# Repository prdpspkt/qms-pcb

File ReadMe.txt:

##This project is done to minimize cost of government office. In market normally Queue Management System costs 65k for manual type and more than 100k for dynamic. Also display, callpad cost extra 20k for each terminal.
This project uses a:
15k Token Printer
10k Android Device as Server
2k Terminal Display
1k Call Pad
-----------------
Total 28k

Paste content from footprints and symbols folder to respective folder in KiCad in documents directory.

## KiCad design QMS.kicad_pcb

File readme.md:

## Queue Management System
This project is done to minimize cost of government office. In market normally Queue Management System costs 65k for manual type and more than 100k for dynamic. Also display, call pad cost extra 20k for each terminal.

### Costing
- 15k Token Printer
- 10k Android Device as Server
- 2k Terminal Display
- 1k Call Pad
...........
- Total 28k

### Installation
Paste content from footprints and symbols folder to respective folder in KiCad in documents directory.

### Programming

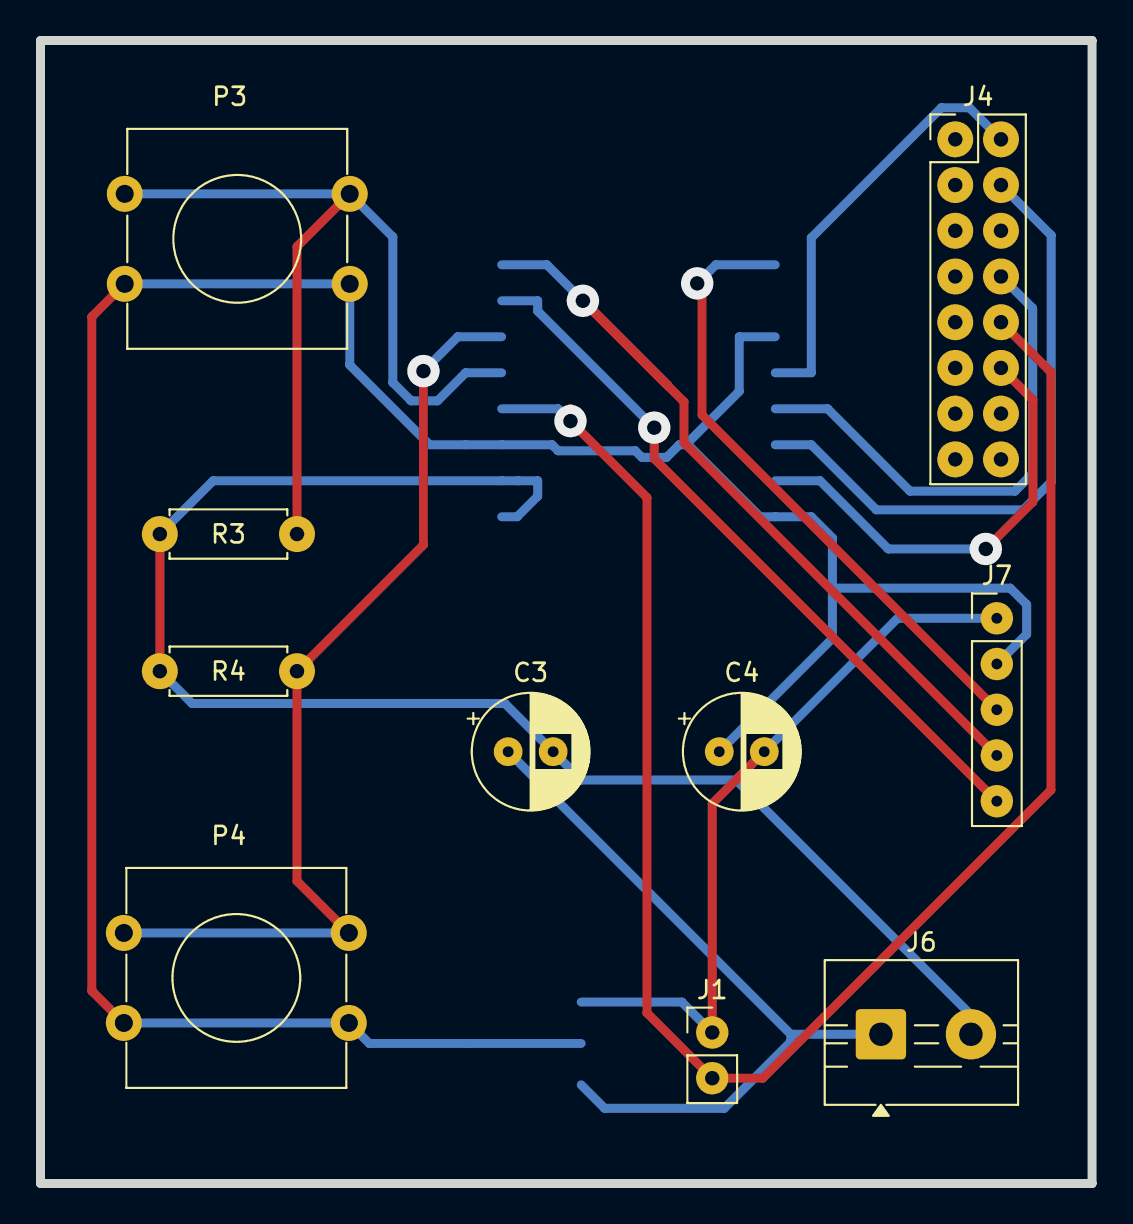
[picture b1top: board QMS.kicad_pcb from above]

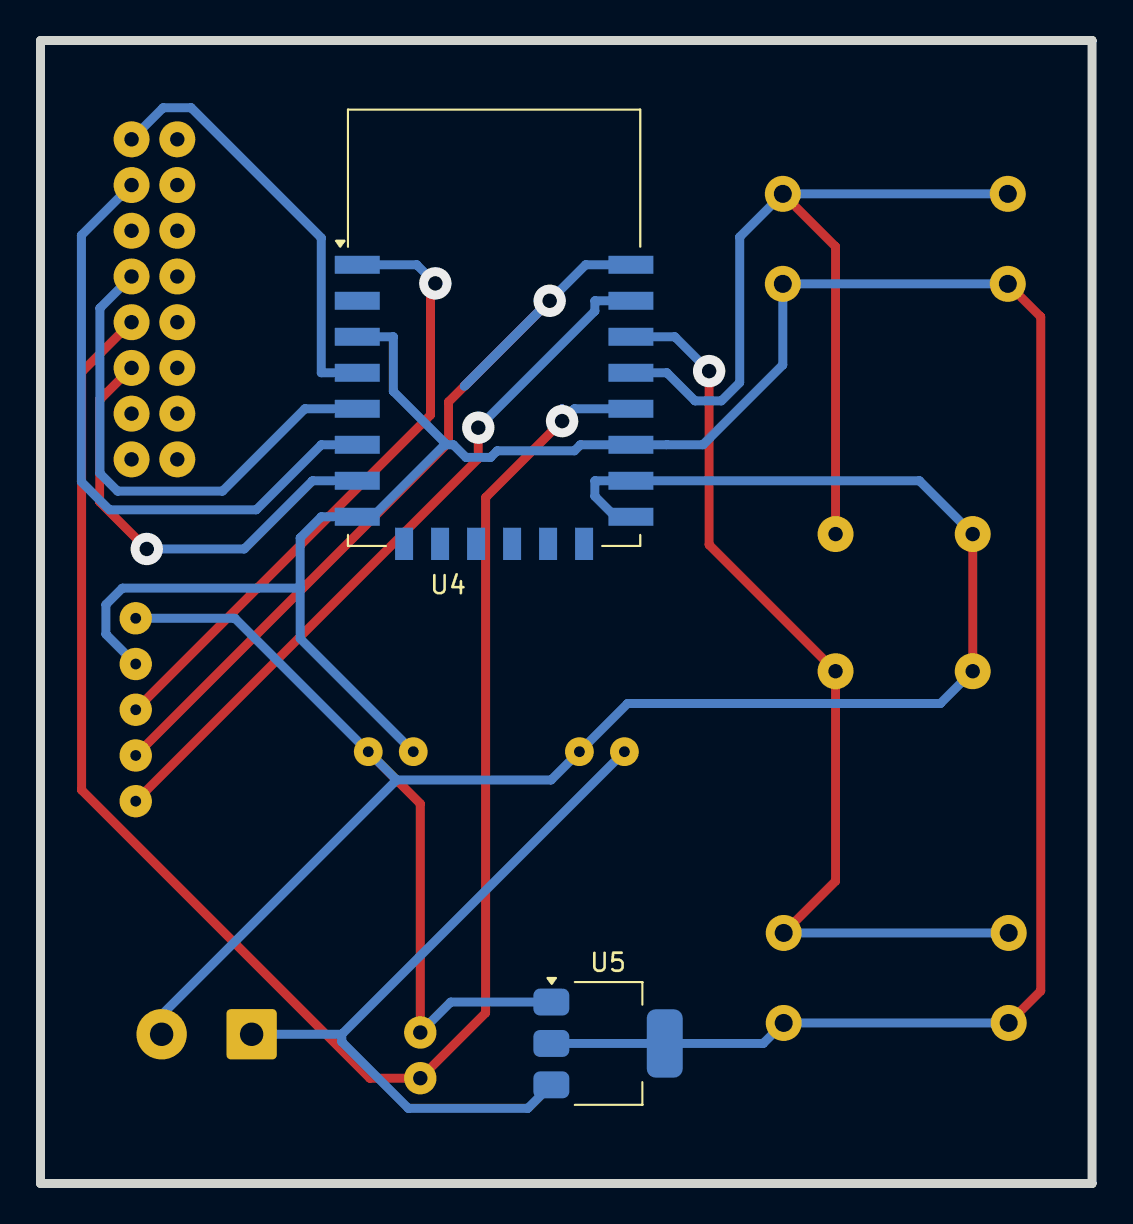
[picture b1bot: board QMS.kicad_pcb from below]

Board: 2 copper layers, 58.4 x 63.5 mm, 12 parts (2 on the bottom side), 13 nets.

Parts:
C3, C4: C_Polarized_US; CP_Radial_D6.3mm_P2.50mm
J1: PINHD_1x5_Male; PinHeader_1x02_P2.54mm_Vertical
J4: Conn_02x08_Top_Bottom; PinHeader 2x8 p2.54mm
J6: Screw_Terminal_01x02; TerminalBlock_MaiXu_MX126-5.0-02P_1x02_P5.00mm
J7: PINHD_1x5_Male; PinHeader_1x05_P2.54mm_Vertical
P3, P4: PUSH_BTN_12x12mm
R3, R4: Resistor; R_Axial_DIN0207_L6.3mm_D2.5mm_P7.62mm_Horizontal
U4: ESP-12E
U5: AMS1117-3.3; SOT-223-3_TabPin2

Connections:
/GPIO0: J1.2, J4.13, U4.18 (GPIO0)
/GPIO1/TXD: J7.4, U4.22 (GPIO1/TXD)
/GPIO3/RXD: J7.5, U4.21 (GPIO3/RXD)
/GPIO4: P3.1, R3.2, U4.19 (GPIO4)
/GPIO5: P4.1, R4.2, U4.20 (GPIO5)
/GPIO12: J4.10, U4.6 (GPIO12)
/GPIO13: J4.14, U4.7 (GPIO13)
/GPIO14: J4.12, U4.5 (GPIO14)
/GPIO16: J4.9, U4.4 (GPIO16)
/RST: J7.3, U4.1 (~RST)
/VCC: C4.1, J7.2, P3.2, P4.2, U4.3 (EN), U4.8 (VCC), U4.17 (GPIO2), U5.2 (VO)
GND: C3.2, C4.2, J1.1, J6.2, J7.1, R3.1, R4.1, U4.15 (GND), U4.16 (GPIO15), U5.1 (GND)
unnamed: C3.1, J6.1, U5.3 (VI)

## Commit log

2025-04-09 project uploaded
2025-04-09 helo
2025-04-10 least
2025-04-10 complete
2025-04-17 completed
2025-04-17 local
2025-04-17 hllo
2025-04-17 deleted unnecessary files
2025-04-17 added readme
2025-04-20 get it
2025-04-25 updated accordin to suggested rules
2025-04-25 removed old backups
2025-04-25 some small fixes
2025-04-25 added gitignore
2025-04-25 modified ignore
2025-04-25 added changes
2025-04-25 modified check
2025-04-25 fixed all errors
2025-04-25 marked as final
